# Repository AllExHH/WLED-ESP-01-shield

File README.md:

# WLED-ESP-01-shield
ESP-01-WLED Shield - double Level shift I try to create the tinyest possible ESP-01 WLED shield for APA102 LED stripes whith 5V to 3V3 Power and logic shifter

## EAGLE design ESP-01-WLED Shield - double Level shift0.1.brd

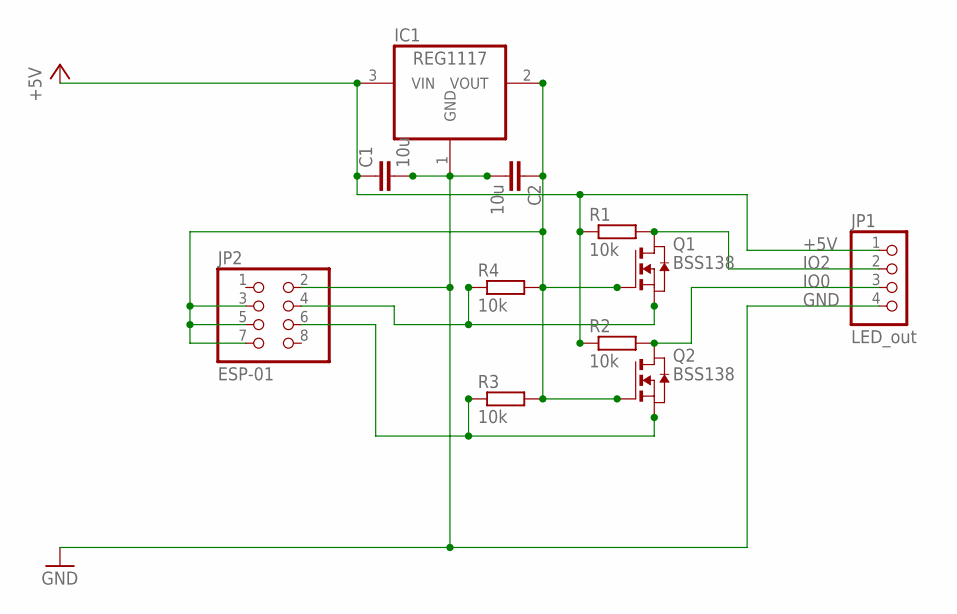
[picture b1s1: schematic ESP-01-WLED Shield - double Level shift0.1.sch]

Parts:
C1, C2: 10u; C0805K
IC1: REG1117; SOT223
JP1: LED_out; 1X04/90
JP2: ESP-01; 2X04
Q1, Q2: BSS138; SOT-23
R1, R2, R3, R4: 10k; R0402

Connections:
+5V: C1.1, IC1.3 (VIN), JP1.1, R1.1, R2.1
GND: C1.2, C2.2, IC1.1 (GND), JP1.4, JP2.2
IO0: JP1.3, Q2.1 (D), R2.2
IO2: JP1.2, Q1.1 (D), R1.2
unnamed: C2.1, IC1.2 (VOUT), JP2.3, JP2.5, JP2.7, Q1.3 (G), Q2.3 (G), R3.2, R4.2
unnamed: JP2.4, Q1.2 (S), R4.1
unnamed: JP2.6, Q2.2 (S), R3.1

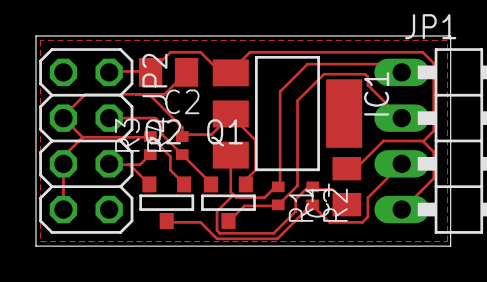
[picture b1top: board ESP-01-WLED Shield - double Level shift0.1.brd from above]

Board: 2 copper layers, 23.0 x 11.7 mm, 11 parts (0 on the bottom side), 7 nets.
